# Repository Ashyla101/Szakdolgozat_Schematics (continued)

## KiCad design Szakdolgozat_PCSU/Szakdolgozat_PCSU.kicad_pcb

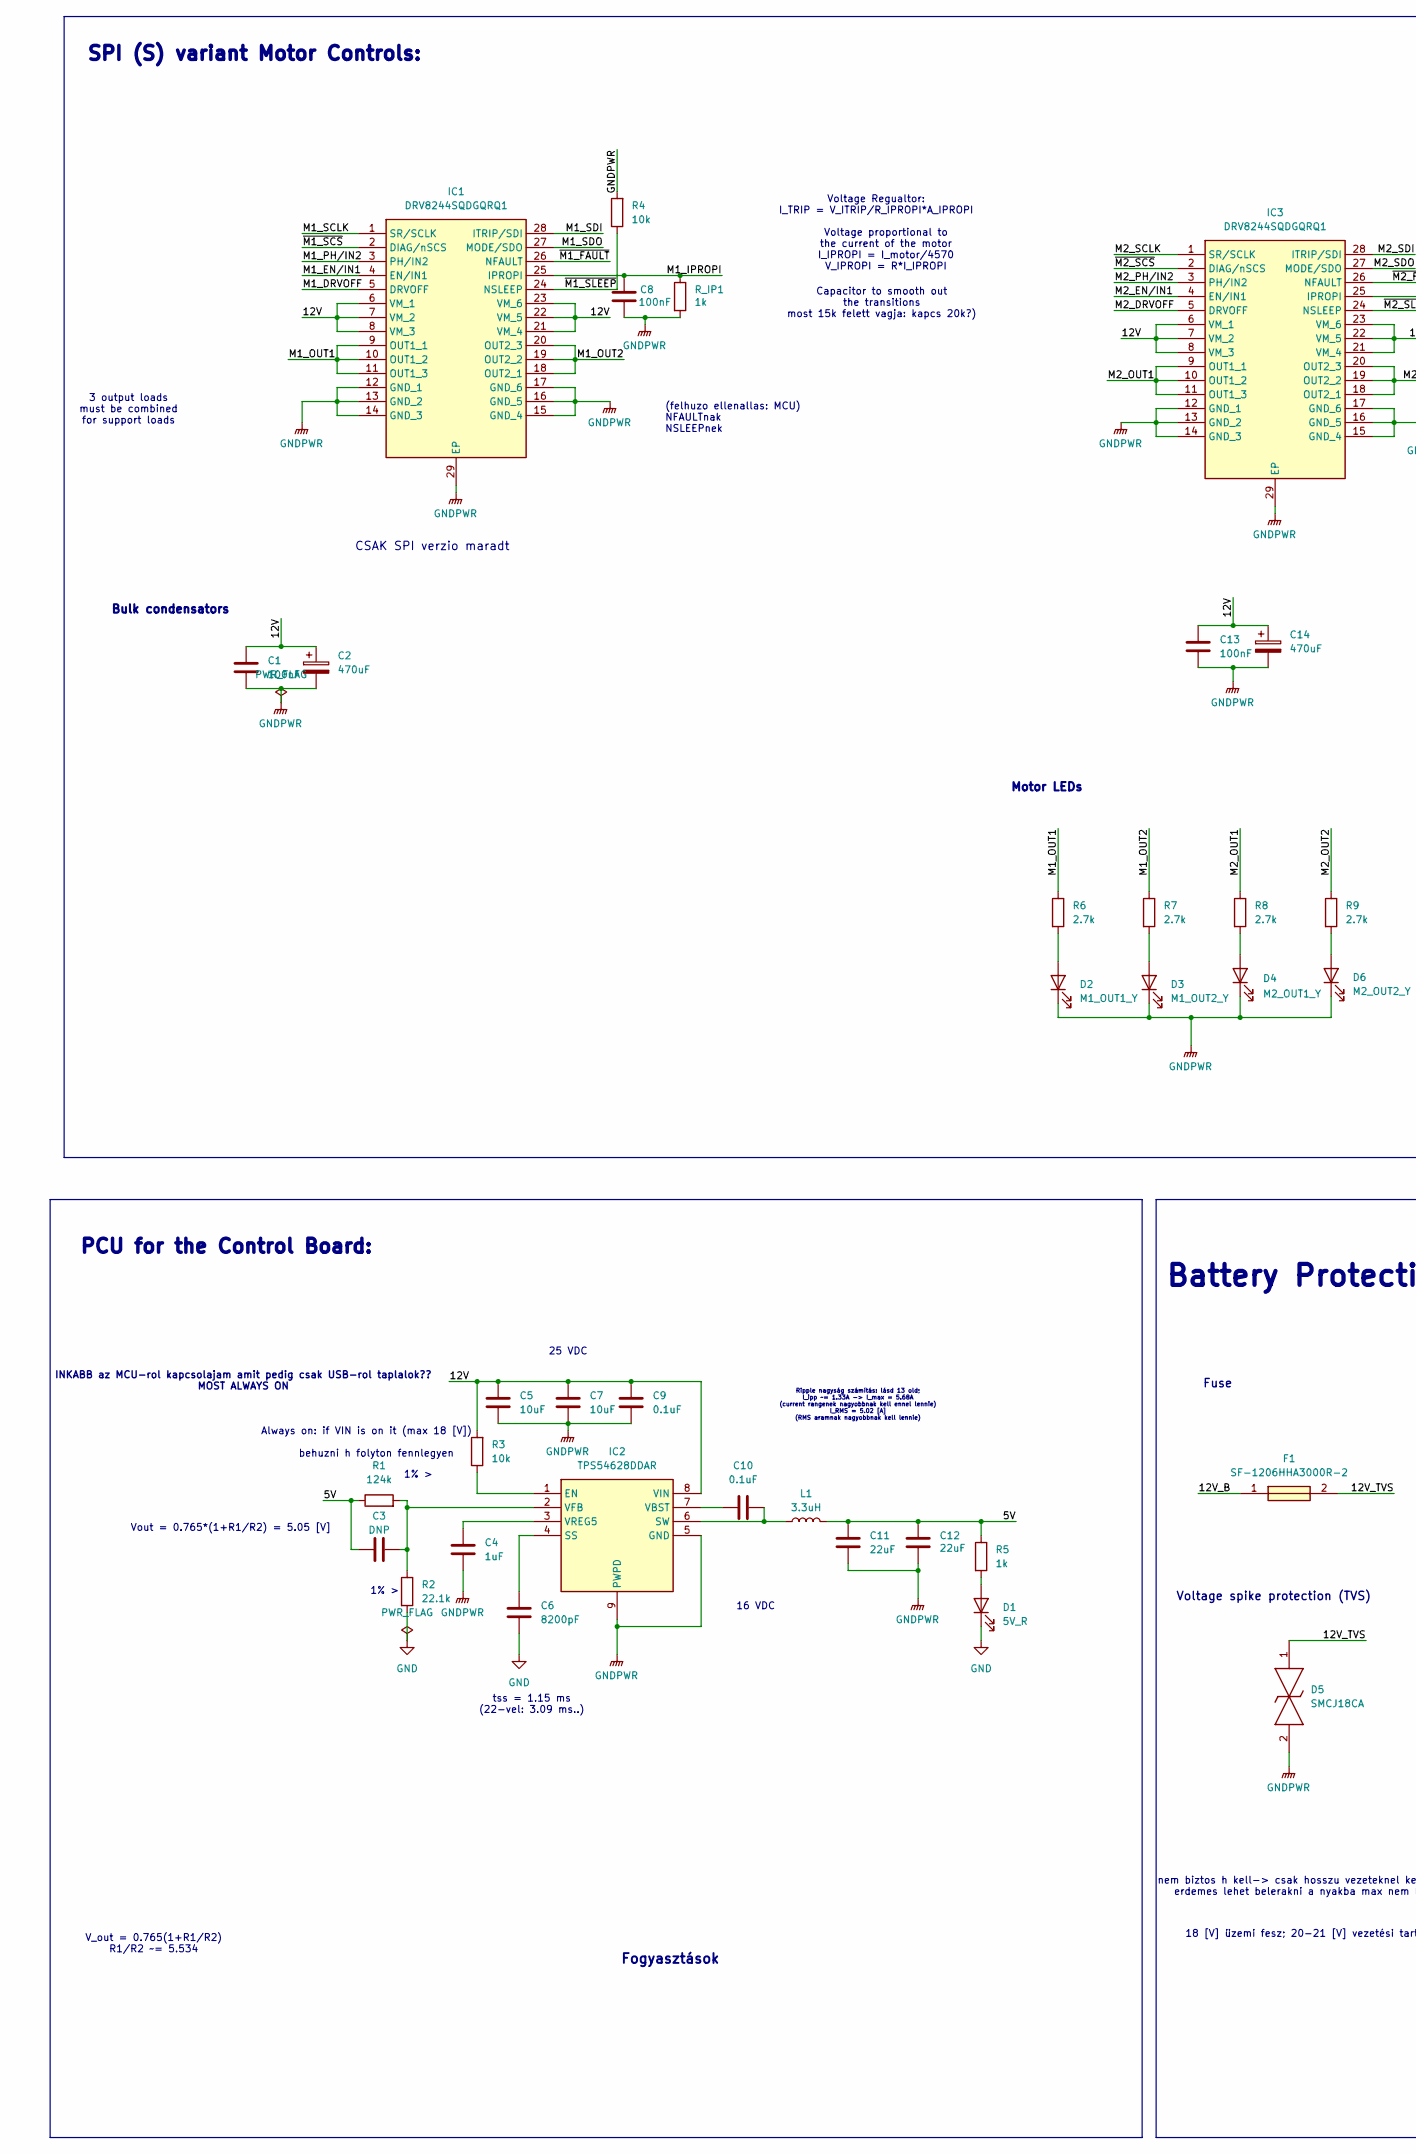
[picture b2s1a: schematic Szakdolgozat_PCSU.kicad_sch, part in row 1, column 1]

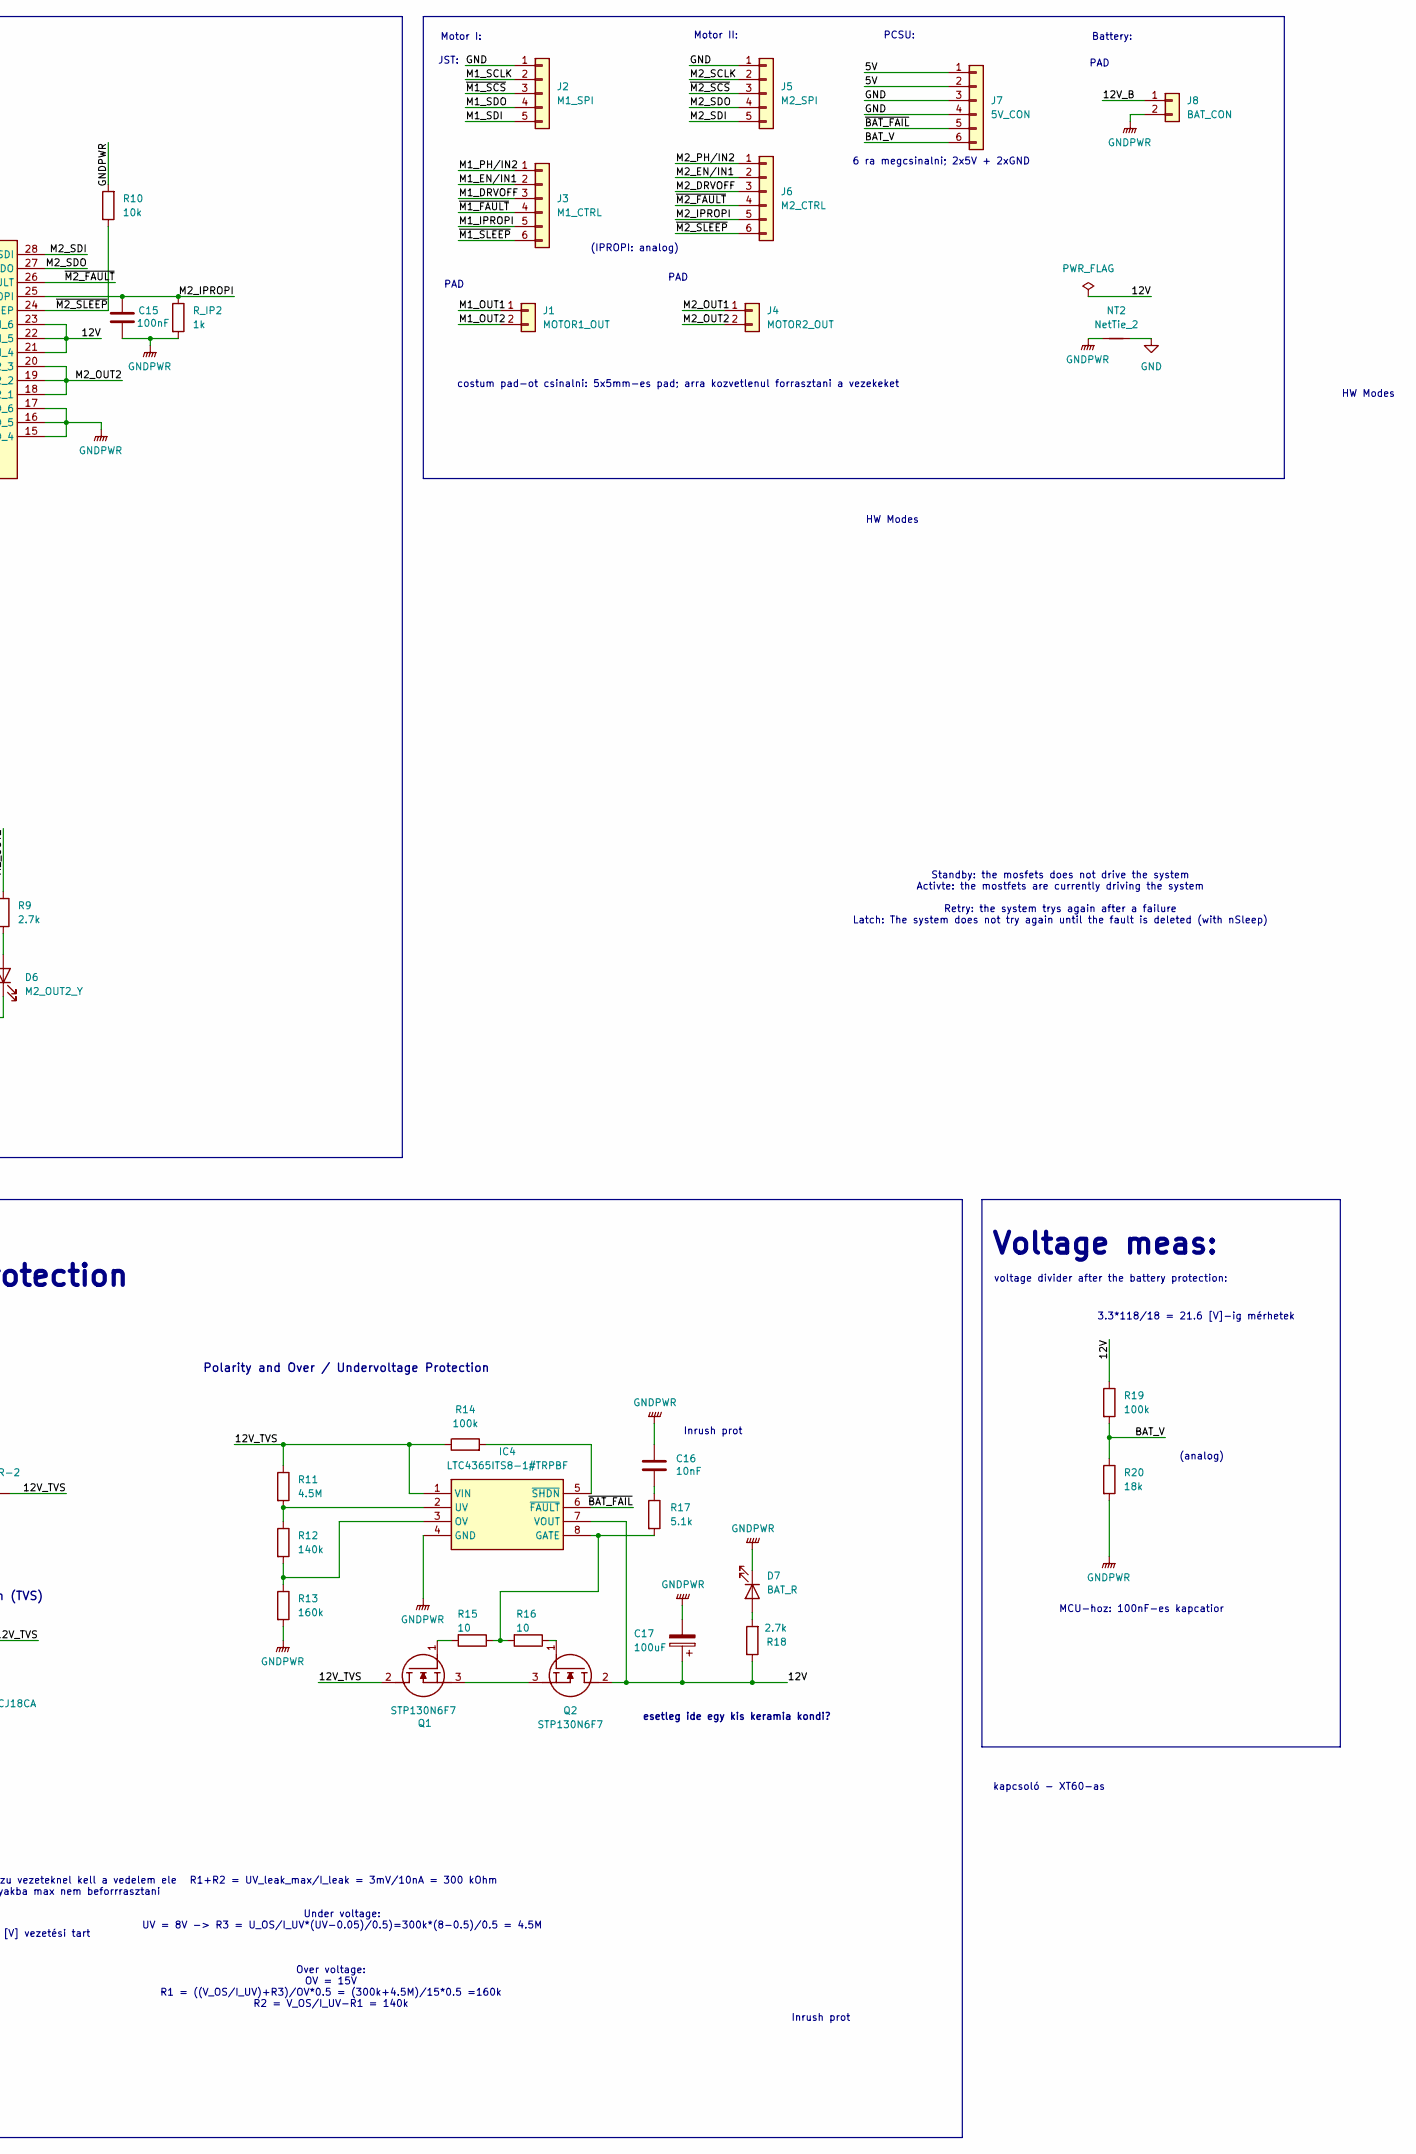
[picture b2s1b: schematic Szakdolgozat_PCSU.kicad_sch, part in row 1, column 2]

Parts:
C1, C8, C13, C15: 100nF; C_0603_1608Metric_Pad1.08x0.95mm_HandSolder
C2, C14: 470uF; CP_Radial_D10.0mm_P5.00mm
C3: DNP; C_0603_1608Metric_Pad1.08x0.95mm_HandSolder
C4: 1uF; C_0603_1608Metric_Pad1.08x0.95mm_HandSolder
C5, C7: 10uF; C_0805_2012Metric_Pad1.18x1.45mm_HandSolder
C6: 8200pF; C_0603_1608Metric_Pad1.08x0.95mm_HandSolder
C9, C10: 0.1uF; C_0603_1608Metric_Pad1.08x0.95mm_HandSolder
C11, C12: 22uF; C_1206_3216Metric_Pad1.33x1.80mm_HandSolder
C16: 10nF; C_0603_1608Metric_Pad1.08x0.95mm_HandSolder
C17: 100uF; CP_Radial_D6.3mm_P2.50mm
D1: 5V_R; LED_0603_1608Metric_Pad1.05x0.95mm_HandSolder
D2: M1_OUT1_Y; LED_0603_1608Metric_Pad1.05x0.95mm_HandSolder
D3: M1_OUT2_Y; LED_0603_1608Metric_Pad1.05x0.95mm_HandSolder
D4: M2_OUT1_Y; LED_0603_1608Metric_Pad1.05x0.95mm_HandSolder
D5: SMCJ18CA; DIONM7959X262N; Mouser Part Number 581-SMCJ18CA
D6: M2_OUT2_Y; LED_0603_1608Metric_Pad1.05x0.95mm_HandSolder
D7: BAT_R; LED_0603_1608Metric_Pad1.05x0.95mm_HandSolder
F1: SF-1206HHA3000R-2; SF1206HHA3000R2; Mouser Part Number 652-SF-1206HHA3000R2
IC1, IC3: DRV8244SQDGQRQ1; SOP50P490X110-29N; Mouser Part Number 595-DRV8244SQDGQRQ1
IC2: TPS54628DDAR; SOIC127P600X170-9N; Mouser Part Number 595-TPS54628DDAR
IC4: LTC4365ITS8-1#TRPBF; SOT65P280X100-8N; Mouser Part Number 584-C4365ITS8-1TRPBF
J1: MOTOR1_OUT; Motor_SolderPad_2Pin
J2: M1_SPI; JST_XH_S5B-XH-A-1_1x05_P2.50mm_Horizontal
J3: M1_CTRL; JST_XH_S6B-XH-A-1_1x06_P2.50mm_Horizontal
J4: MOTOR2_OUT; Motor_SolderPad_2Pin
J5: M2_SPI; JST_XH_S5B-XH-A-1_1x05_P2.50mm_Horizontal
J6: M2_CTRL; JST_XH_S6B-XH-A-1_1x06_P2.50mm_Horizontal
J7: 5V_CON; JST_XH_S6B-XH-A-1_1x06_P2.50mm_Horizontal
J8: BAT_CON; Battery_SolderPad_2Pin
L1: 3.3uH; BMRA000606303R3MA1
NT2: NetTie_2; Untitled
Q1, Q2: STP130N6F7; TO255P460X1020X2008-3P; Mouser Part Number 511-STP130N6F7
R1: 124k; R_0603_1608Metric_Pad0.98x0.95mm_HandSolder
R2: 22.1k; R_0603_1608Metric_Pad0.98x0.95mm_HandSolder
R3, R4, R10: 10k; R_0603_1608Metric_Pad0.98x0.95mm_HandSolder
R5: 1k; R_0603_1608Metric_Pad0.98x0.95mm_HandSolder
R6, R7, R8, R9, R18: 2.7k; R_0603_1608Metric_Pad0.98x0.95mm_HandSolder
R11: 4.5M; R_0603_1608Metric_Pad0.98x0.95mm_HandSolder
R12: 140k; R_0603_1608Metric_Pad0.98x0.95mm_HandSolder
R13: 160k; R_0603_1608Metric_Pad0.98x0.95mm_HandSolder
R14, R19: 100k; R_0603_1608Metric_Pad0.98x0.95mm_HandSolder
R15, R16: 10; R_0603_1608Metric_Pad0.98x0.95mm_HandSolder
R17: 5.1k; R_0603_1608Metric_Pad0.98x0.95mm_HandSolder
R20: 18k; R_0603_1608Metric_Pad0.98x0.95mm_HandSolder
R_IP1, R_IP2: 1k; R_0603_1608Metric_Pad0.98x0.95mm_HandSolder

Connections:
/5V: C3.1, C11.2, C12.2, J7.1, J7.2, L1.2, R1.1, R5.1
/12V: C1.1, C2.1, C5.1, C7.1, C9.1, C13.1, C14.1, C17.1, IC1.6 (VM_1), IC1.7 (VM_2), IC1.8 (VM_3), IC1.21 (VM_4), IC1.22 (VM_5), IC1.23 (VM_6), IC2.8 (VIN), IC3.6 (VM_1), IC3.7 (VM_2), IC3.8 (VM_3), IC3.21 (VM_4), IC3.22 (VM_5), IC3.23 (VM_6), IC4.7 (VOUT), Q2.2 (D), R3.2, R18.1, R19.1
/12V_B: F1.1, J8.1
/12V_TVS: D5.1, F1.2, IC4.1 (VIN), Q1.2 (D), R11.1, R14.1
/BAT_V: J7.6, R19.2, R20.1
/M1_DRVOFF: IC1.5 (DRVOFF), J3.3
/M1_EN/IN1: IC1.4 (EN/IN1), J3.2
/M1_IPROPI: C8.1, IC1.25 (IPROPI), J3.5, R_IP1.1
/M1_OUT1: IC1.9 (OUT1_1), IC1.10 (OUT1_2), IC1.11 (OUT1_3), J1.1, R6.1
/M1_OUT2: IC1.18 (OUT2_1), IC1.19 (OUT2_2), IC1.20 (OUT2_3), J1.2, R7.1
/M1_PH/IN2: IC1.3 (PH/IN2), J3.1
/M1_SCLK: IC1.1 (SR/SCLK), J2.2
/M1_SDI: IC1.28 (ITRIP/SDI), J2.5
/M1_SDO: IC1.27 (MODE/SDO), J2.4
/M2_DRVOFF: IC3.5 (DRVOFF), J6.3
/M2_EN/IN1: IC3.4 (EN/IN1), J6.2
/M2_IPROPI: C15.1, IC3.25 (IPROPI), J6.5, R_IP2.1
/M2_OUT1: IC3.9 (OUT1_1), IC3.10 (OUT1_2), IC3.11 (OUT1_3), J4.1, R8.1
/M2_OUT2: IC3.18 (OUT2_1), IC3.19 (OUT2_2), IC3.20 (OUT2_3), J4.2, R9.1
/M2_PH/IN2: IC3.3 (PH/IN2), J6.1
/M2_SCLK: IC3.1 (SR/SCLK), J5.2
/M2_SDI: IC3.28 (ITRIP/SDI), J5.5
/M2_SDO: IC3.27 (MODE/SDO), J5.4
/~BAT_FAIL: IC4.6 (~FAULT), J7.5
/~M1_FAULT: IC1.26 (NFAULT), J3.4
/~M1_SCS: IC1.2 (DIAG/nSCS), J2.3
/~M1_SLEEP: IC1.24 (NSLEEP), J3.6, R4.1
/~M2_FAULT: IC3.26 (NFAULT), J6.4
/~M2_SCS: IC3.2 (DIAG/nSCS), J5.3
/~M2_SLEEP: IC3.24 (NSLEEP), J6.6, R10.1
GND: C6.2, D1.1 (K), J2.1, J5.1, J7.3, J7.4, NT2.2, R2.2
GNDPWR: C1.2, C2.2, C4.2, C5.2, C7.2, C8.2, C9.2, C11.1, C12.1, C13.2, C14.2, C15.2, C16.2, C17.2, D2.1 (K), D3.1 (K), D4.1 (K), D5.2, D6.1 (K), D7.1 (K), IC1.12 (GND_1), IC1.13 (GND_2), IC1.14 (GND_3), IC1.15 (GND_4), IC1.16 (GND_5), IC1.17 (GND_6), IC1.29 (EP), IC2.5 (GND), IC2.9 (PWPD), IC3.12 (GND_1), IC3.13 (GND_2), IC3.14 (GND_3), IC3.15 (GND_4), IC3.16 (GND_5), IC3.17 (GND_6), IC3.29 (EP), IC4.4 (GND), J8.2, NT2.1, R4.2, R10.2, R13.2, R20.2, R_IP1.2, R_IP2.2
unnamed: C16.1, R17.1
unnamed: D1.2 (A), R5.2
unnamed: D2.2 (A), R6.2
unnamed: D3.2 (A), R7.2
unnamed: D4.2 (A), R8.2
unnamed: D6.2 (A), R9.2
unnamed: D7.2 (A), R18.2
unnamed: IC2.1 (EN), R3.1
unnamed: C6.1, IC2.4 (SS)
unnamed: C10.2, IC2.6 (SW), L1.1
unnamed: C10.1, IC2.7 (VBST)
unnamed: C3.2, IC2.2 (VFB), R1.2, R2.1
unnamed: C4.1, IC2.3 (VREG5)
unnamed: IC4.8 (GATE), R15.1, R16.2, R17.2
unnamed: IC4.3 (OV), R12.2, R13.1
unnamed: IC4.2 (UV), R11.2, R12.1
unnamed: IC4.5 (~SHDN), R14.2
unnamed: Q1.1 (G), R15.2
unnamed: Q1.3 (S), Q2.3 (S)
unnamed: Q2.1 (G), R16.1

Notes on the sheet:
18 [V] üzemi fesz; 20-21 [V] vezetési tart
behuzni h folyton fennlegyen
Battery Protection
costum pad-ot csinalni: 5x5mm-es pad; arra kozvetlenul forrasztani a vezekeket
tss = 1.15 ms (22-vel: 3.09 ms..)
PCSU:
Polarity and Over / Undervoltage Protection
PAD
CSAK SPI verzio maradt
Voltage Regualtor: I_TRIP = V_ITRIP/R_IPROPI*A_IPROPI
1% >
(IPROPI: analog)
MCU-hoz: 100nF-es kapcatior
HW Modes
Under voltage: UV = 8V -> R3 = U_OS/I_UV*(UV-0.05)/0.5)=300k*(8-0.5)/0.5 = 4.5M
Motor LEDs
Voltage spike protection (TVS)
Voltage meas:
Battery:
(analog)
V_out = 0.765(1+R1/R2) R1/R2 ~= 5.534
PCU for the Control Board:
R1+R2 = UV_leak_max/I_leak = 3mV/10nA = 300 kOhm
INKABB az MCU-rol kapcsolajam amit pedig csak USB-rol taplalok?? MOST ALWAYS ON
Ripple nagyság számítás: lásd 13 old; I_ipp ~= 1.33A -> I_max = 5.68A (current rangenek nagyobbnak kell ennel lennie) I_RMS = 5.02 [A] (RMS aramnak nagyobbnak kell lennie)
kapcsoló - XT60-as
16 VDC
Always on: if VIN is on it (max 18 [V])
Fuse
Capacitor to smooth out the transitions most 15k felett vagja: kapcs 20k?)
6 ra megcsinalni; 2x5V + 2xGND
JST:
3 output loads must be combined for support loads
Bulk condensators
(felhuzo ellenallas: MCU) NFAULTnak NSLEEPnek
nem biztos h kell-> csak hosszu vezeteknel kell a vedelem ele erdemes lehet belerakni a nyakba max nem beforrrasztani
Motor I:
SPI (S) variant Motor Controls:
Standby: the mosfets does not drive the system Activte: the mostfets are currently driving the system Retry: the system trys again after a failure Latch: The system does not try again until the fault is deleted (with nSleep)
voltage divider after the battery protection:

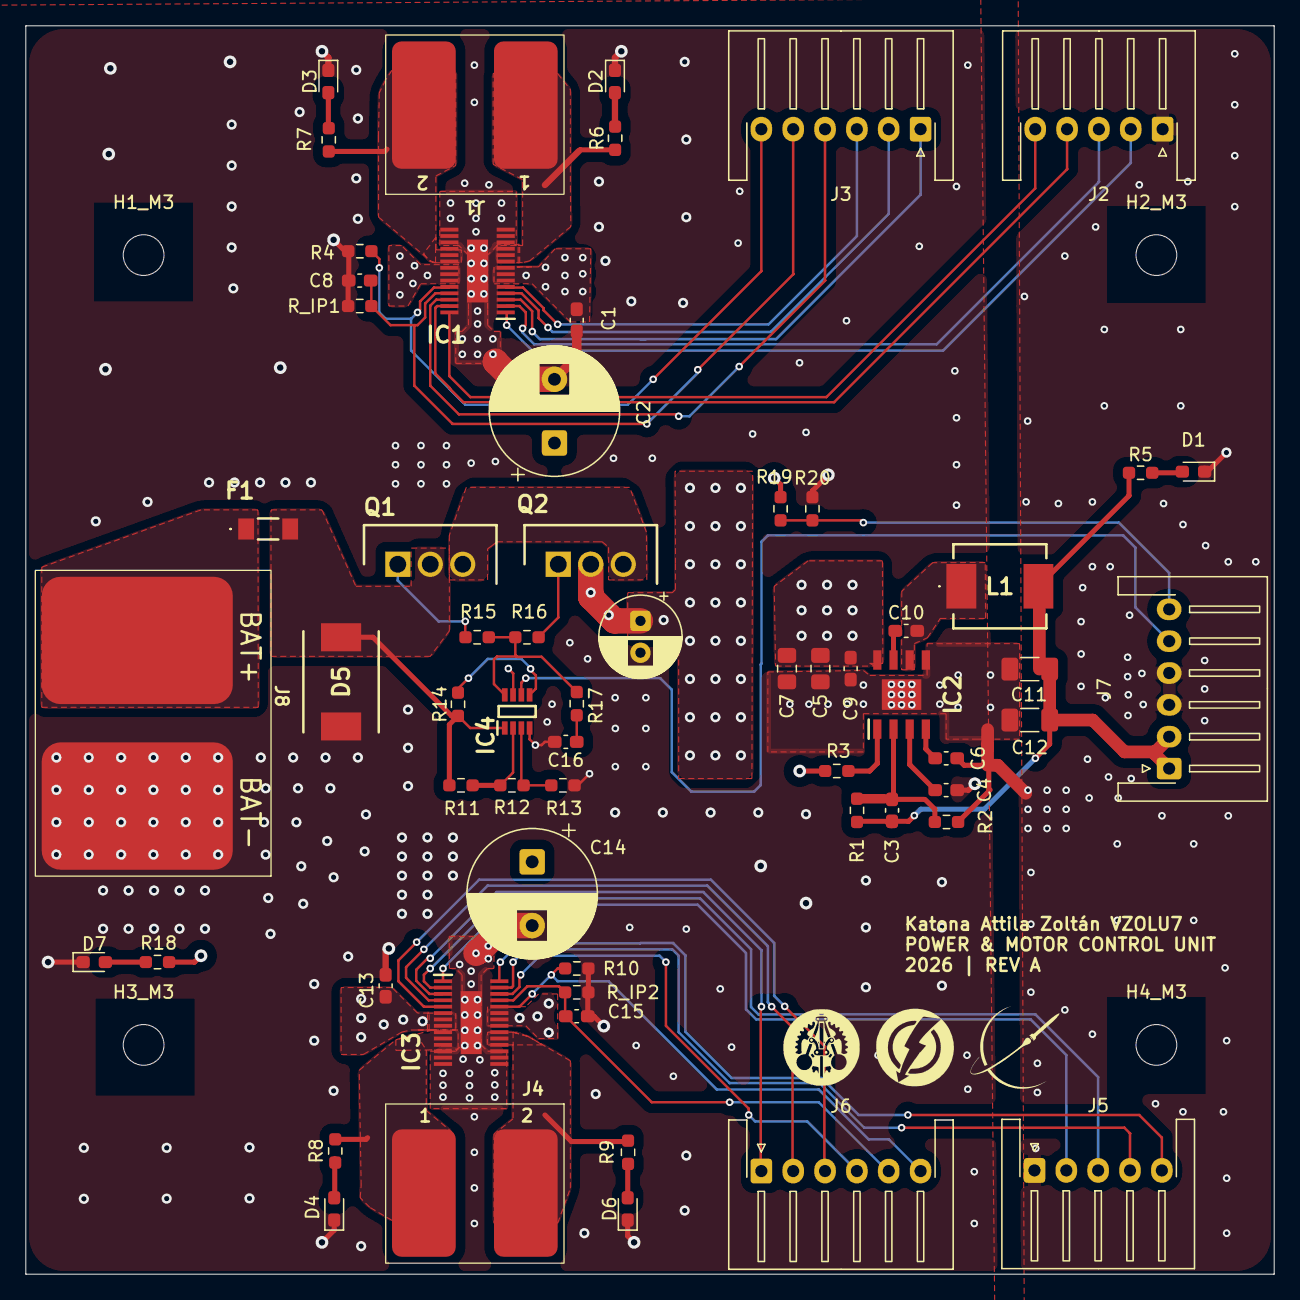
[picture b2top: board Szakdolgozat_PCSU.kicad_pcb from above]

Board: 4 copper layers, 98.0 x 98.0 mm, 67 parts (0 on the bottom side), 52 nets.

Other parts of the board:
H1_M3, H2_M3, H3_M3, H4_M3: MountingHole_3.2mm_M3

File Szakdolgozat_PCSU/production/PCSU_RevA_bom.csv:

Designator,Footprint,Quantity,Value,LCSC Part #
"C1, C13, C15, C8",0603,4,100nF,
"C10, C9",0603,2,0.1uF,
"C11, C12",1206,2,22uF,
"C14, C2",CP_Radial_D10.0mm_P5.00mm,2,470uF,
C16,0603,1,10nF,
C17,CP_Radial_D6.3mm_P2.50mm,1,100uF,
C3,0603,1,DNP,
C4,0603,1,1uF,
"C5, C7",0805,2,10uF,
C6,0603,1,8200pF,
D1,0603,1,5V_R,
D2,0603,1,M1_OUT1_Y,
D3,0603,1,M1_OUT2_Y,
D4,0603,1,M2_OUT1_Y,
D5,DIONM7959X262N,1,SMCJ18CA,
D6,0603,1,M2_OUT2_Y,
D7,0603,1,BAT_R,
F1,SF1206HHA3000R2,1,SF-1206HHA3000R-2,
"IC1, IC3",SOP50P490X110-29N,2,DRV8244SQDGQRQ1,
IC2,SOIC127P600X170-9N,1,TPS54628DDAR,
IC4,SOT65P280X100-8N,1,LTC4365ITS8-1#TRPBF,
J1,Motor_SolderPad_2Pin,1,MOTOR1_OUT,
J2,JST_XH_S5B-XH-A-1_1x05_P2.50mm_Horizontal,1,M1_SPI,
J3,JST_XH_S6B-XH-A-1_1x06_P2.50mm_Horizontal,1,M1_CTRL,
J4,Motor_SolderPad_2Pin,1,MOTOR2_OUT,
J5,JST_XH_S5B-XH-A-1_1x05_P2.50mm_Horizontal,1,M2_SPI,
J6,JST_XH_S6B-XH-A-1_1x06_P2.50mm_Horizontal,1,M2_CTRL,
J7,JST_XH_S6B-XH-A-1_1x06_P2.50mm_Horizontal,1,5V_CON,
J8,Battery_SolderPad_2Pin,1,BAT_CON,
L1,BMRA000606303R3MA1,1,3.3uH,
NT2,Untitled,1,NetTie_2,
"Q1, Q2",TO255P460X1020X2008-3P,2,STP130N6F7,
R1,0603,1,124k,
"R10, R3, R4",0603,3,10k,
R11,0603,1,4.5M,
R12,0603,1,140k,
R13,0603,1,160k,
"R14, R19",0603,2,100k,
"R15, R16",0603,2,10,
R17,0603,1,5.1k,
"R18, R6, R7, R8, R9",0603,5,2.7k,
R2,0603,1,22.1k,
R20,0603,1,18k,
"R5, R_IP1, R_IP2",0603,3,1k,
